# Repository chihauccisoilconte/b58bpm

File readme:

This repository contains the documents relative to the research project named "Below 38BPM" 

the files are shared under GPLv3 license

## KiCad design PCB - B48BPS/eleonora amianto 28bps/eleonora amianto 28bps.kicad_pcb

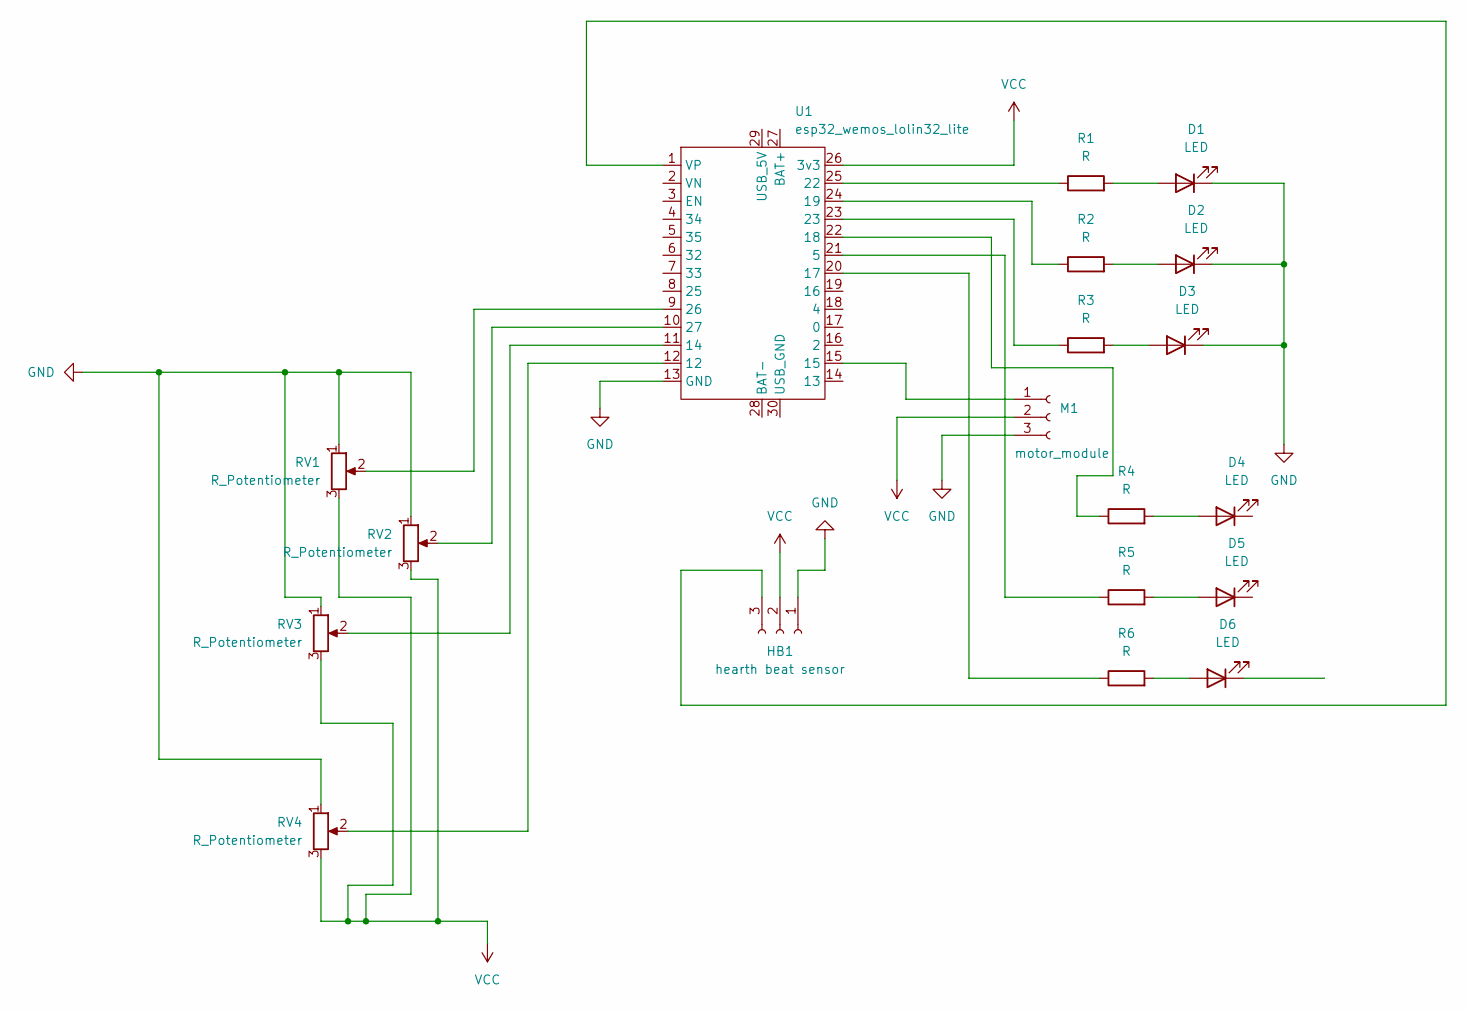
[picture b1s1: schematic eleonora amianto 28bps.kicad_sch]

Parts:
D1, D2, D3, D4, D5, D6: LED; LED_D3.0mm
HB1: hearth beat sensor; PinHeader_1x03_P2.00mm_Vertical
M1: motor_module; PinHeader_1x03_P2.00mm_Vertical
R1, R2, R3, R4, R5, R6: R; R_Axial_DIN0207_L6.3mm_D2.5mm_P10.16mm_Horizontal
RV1, RV2, RV3, RV4: R_Potentiometer; PinHeader_1x03_P2.00mm_Vertical
U1: esp32_wemos_lolin32_lite

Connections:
GND: D1.1 (K), D2.1 (K), D3.1 (K), HB1.1, M1.3, RV1.1, RV2.1, RV3.1, RV4.1, U1.13 (GND)
unnamed: D1.2 (A), R1.2
unnamed: D2.2 (A), R2.2
unnamed: D3.2 (A), R3.2
unnamed: D4.2 (A), R4.2
unnamed: D5.2 (A), R5.2
unnamed: D6.2 (A), R6.2
unnamed: HB1.3, U1.1 (VP)
unnamed: M1.1, U1.15
unnamed: R1.1, U1.25 (22)
unnamed: R2.1, U1.24 (19)
unnamed: R3.1, U1.23
unnamed: R4.1, U1.22 (18)
unnamed: R5.1, U1.21 (5)
unnamed: R6.1, U1.20 (17)
unnamed: RV1.2, U1.9 (26)
unnamed: RV2.2, U1.10 (27)
unnamed: RV3.2, U1.11 (14)
unnamed: RV4.2, U1.12
VCC: HB1.2, M1.2, RV1.3, RV2.3, RV3.3, RV4.3, U1.26 (3v3)

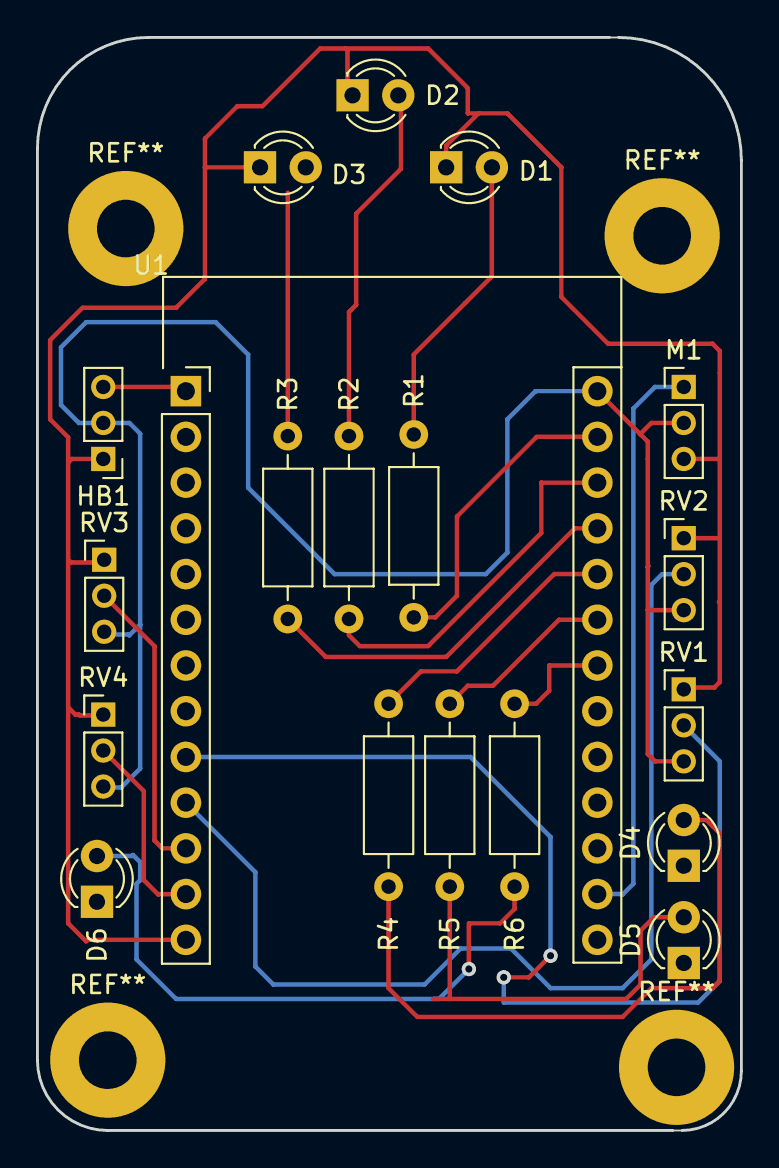
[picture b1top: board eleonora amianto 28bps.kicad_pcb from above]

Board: 2 copper layers, 39.1 x 60.7 mm, 19 parts (0 on the bottom side), 20 nets.
